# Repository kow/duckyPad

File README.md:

# duckypad: Scriptable Mechanical Keypad with RGB Backlight

duckypad is a mechanical keypad with RGB backlight, OLED screen, and 15 keys. Each key can execute a script when pressed.

The scripts can be as simple as shortcuts like `ctrl+c`, or as complex as [creating root backdoors](https://github.com/hak5darren/USB-Rubber-Ducky/wiki/Payload---OSX-Root-Backdoor) or [grabbing passwords](https://github.com/hak5darren/USB-Rubber-Ducky/wiki/Payload---download-mimikatz%2C-grab-passwords-and-email-them-via-gmail). It's all customizable by you.

Multiple profiles are supported, for different programs/environments.

## Features

* 15 mechanical switches
* Individually addressable RGB backlights with animations
* OLED screen displaying current profile and key functions
* SD card script storage
* Standard duckyscript parsed onboard
* Multiple profiles
* USB-C connector

## Video

Here's a silly video showing duckypad in action, as well as the timelapse of me building it.

https://www.youtube.com/watch?v=EGLLCtRuEuM

## Getting started

Please see [this guide](./getting_started.md) on how to use your duckypad.

## Making one yourself

Please see [this guide](./build_it_yourself.md).

## Questions?

Feel free to ask in the issue section, or email me at `dekunukem__gmail__com`.

## kowmod1 ##

replaced LCD with cheaper 4 pin version, uses any ~$3 128x64 oled LCD with VCC,GND,SCL,SDA pinout order (https://www.ebay.ca/itm/0-96-I2C-IIC-SPI-Serial-128X64-White-OLED-LCD-LED-Display-Module-for-Arduino-LR/392728983410)
replaced sk6812 mini with ws2812b mini, added gerber, bom, and cpl for jlcpcb assembly

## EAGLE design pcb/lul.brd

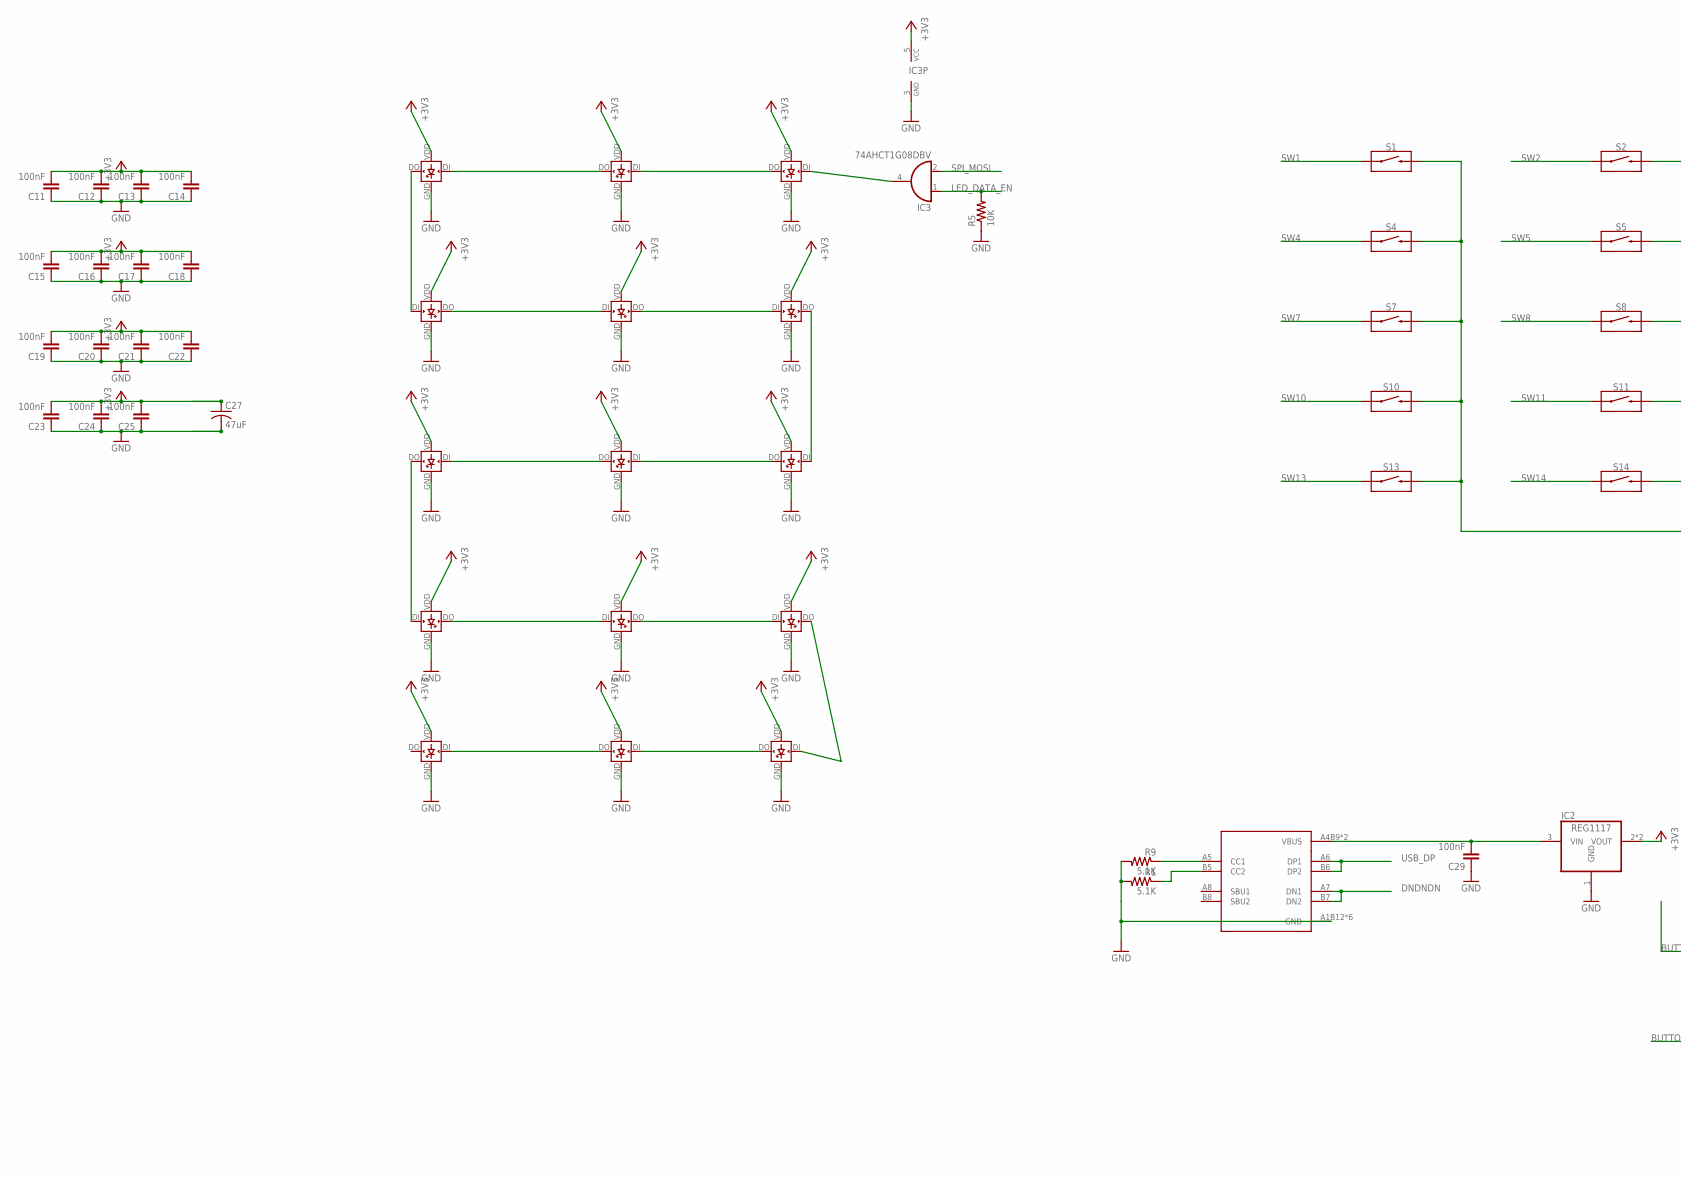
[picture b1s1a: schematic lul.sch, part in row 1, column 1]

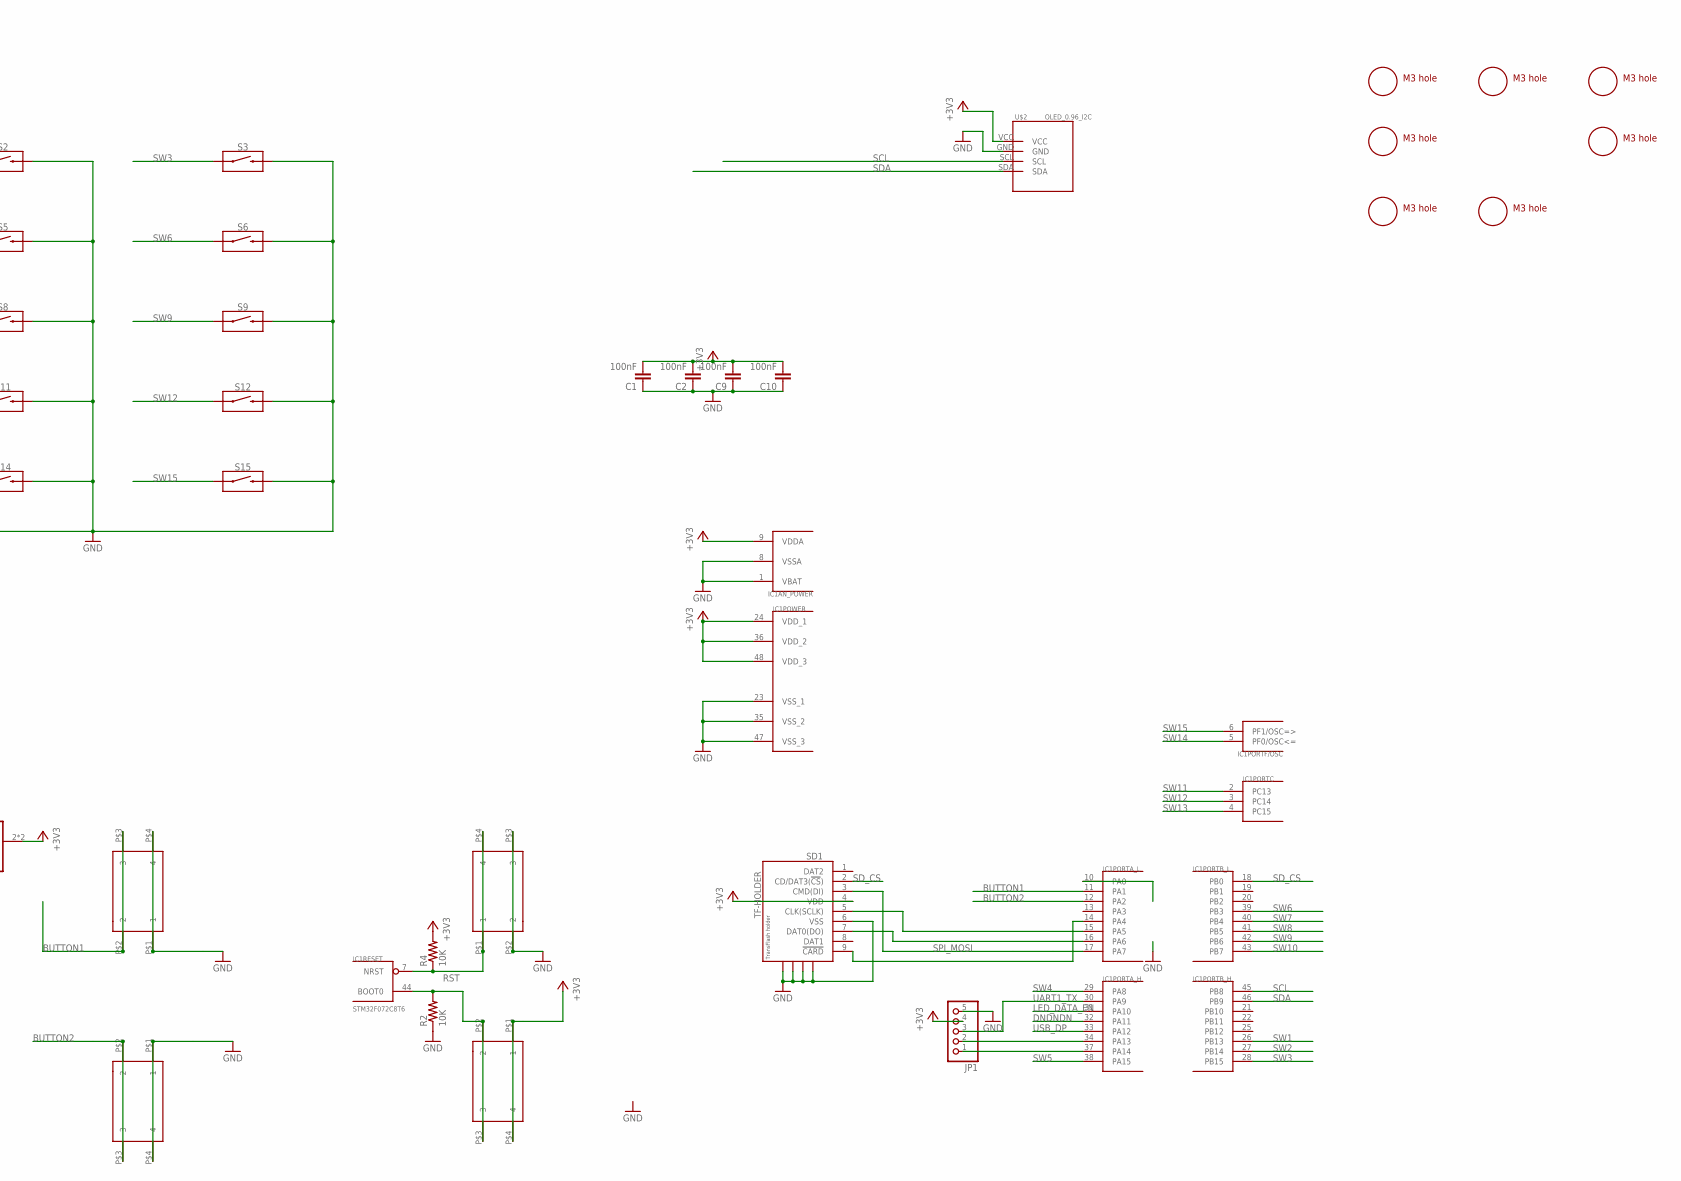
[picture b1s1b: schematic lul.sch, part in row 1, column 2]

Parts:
C1, C2, C9, C10, C11, C12, C13, C14, C15, C16, C17, C18, C19, C20, C21, C22, C23, C24, C25, C29: 100nF; 0805@1
C27: 47uF; C1210
IC1: STM32F072C8T6; TQFP48
IC2: REG1117; SOT223
IC3: 74AHCT1G08DBV; SOT23-5
JP1: PINHD-1X5; 1X05
LED1, LED2, LED3, LED4, LED5, LED6, LED7, LED8, LED9, LED10, LED11, LED12, LED13, LED14, LED15: WS2812B-MINI
R1, R9: 5.1K; 0805
R2, R4, R5: 10K; 0805
S1, S2, S3, S4, S5, S6, S7, S8, S9, S10, S11, S12, S13, S14, S15: CHERRY-MX-LED
SD1: TF-HOLDER; TF-PULL
SW1, SW2, SW3, SW4: 324_SW324_SWITCH_FOOT_HOLE; 342_SWICH_FOOT_HOLE
U2: USBC_16P; USBC_16P_FOOT
U$2: OLED_0.96_I2C
U$7, U$9, U$10, U$11, U$14, U$15, U$16: M3_MOUNTING_HOLE; M3_MOUNTING_HOLE_PACK

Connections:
+3V3: C1.2, C2.2, C9.2, C10.2, C11.2, C12.2, C13.2, C14.2, C15.2, C16.2, C17.2, C18.2, C19.2, C20.2, C21.2, C22.2, C23.2, C24.2, C25.2, C27.1, IC1.9 (VDDA), IC1.24 (VDD_1), IC1.36 (VDD_2), IC1.48 (VDD_3), IC2.2 (VOUT), IC2.4 (VOUT), IC3.5 (VCC), JP1.4, LED1.VDD, LED2.VDD, LED3.VDD, LED4.VDD, LED5.VDD, LED6.VDD, LED7.VDD, LED8.VDD, LED9.VDD, LED10.VDD, LED11.VDD, LED12.VDD, LED13.VDD, LED14.VDD, LED15.VDD, R4.2, SD1.4 (VDD), SW1.P$1 (1), SW1.P$4 (4), U$2.VCC
BUTTON1: IC1.11 (PA1), SW3.P$2 (2), SW3.P$3 (3)
BUTTON2: IC1.12 (PA2), SW4.P$2 (2), SW4.P$3 (3)
DNDNDN: IC1.32 (PA11), U2.A7 (DN1), U2.B7 (DN2)
GND: C1.1, C2.1, C9.1, C10.1, C11.1, C12.1, C13.1, C14.1, C15.1, C16.1, C17.1, C18.1, C19.1, C20.1, C21.1, C22.1, C23.1, C24.1, C25.1, C27.2, C29.1, IC1.1 (VBAT), IC1.8 (VSSA), IC1.23 (VSS_1), IC1.35 (VSS_2), IC1.47 (VSS_3), IC2.1 (GND), IC3.3 (GND), JP1.5, LED1.GND, LED2.GND, LED3.GND, LED4.GND, LED5.GND, LED6.GND, LED7.GND, LED8.GND, LED9.GND, LED10.GND, LED11.GND, LED12.GND, LED13.GND, LED14.GND, LED15.GND, R1.2, R2.1, R5.1, R9.2, S1.S2, S2.S2, S3.S2, S4.S2, S5.S2, S6.S2, S7.S2, S8.S2, S9.S2, S10.S2, S11.S2, S12.S2, S13.S2, S14.S2, S15.S2, SD1.6 (VSS), SD1.S1, SD1.S2, SD1.S3, SD1.S4, SW2.P$2 (2), SW2.P$3 (3), SW3.P$1 (1), SW3.P$4 (4), SW4.P$1 (1), SW4.P$4 (4), U2.A1B12 (GND), U2.B11A12 (GND), U2.P$13 (GND), U2.P$14 (GND), U2.P$15 (GND), U2.P$16 (GND), U$2.GND
LED_DATA_EN: IC1.31 (PA10), IC3.1 (I0), R5.2
unnamed: C29.2, IC2.3 (VIN), U2.A4B9 (VBUS), U2.B4A9 (VBUS)
unnamed: IC1.44 (BOOT0), R2.2, SW1.P$2 (2), SW1.P$3 (3)
unnamed: IC1.15 (PA5), SD1.5 (CLK(SCLK))
unnamed: LED2.DI (DIN), LED3.DO (DOUT)
unnamed: IC1.16 (PA6), SD1.7 (DAT0(DO))
unnamed: IC1.14 (PA4), SD1.9 (!CARD)
unnamed: LED1.DI (DIN), LED2.DO (DOUT)
unnamed: LED1.DO (DOUT), LED4.DI (DIN)
unnamed: LED4.DO (DOUT), LED5.DI (DIN)
unnamed: LED5.DO (DOUT), LED6.DI (DIN)
unnamed: LED6.DO (DOUT), LED9.DI (DIN)
unnamed: LED8.DI (DIN), LED9.DO (DOUT)
unnamed: LED7.DI (DIN), LED8.DO (DOUT)
unnamed: LED7.DO (DOUT), LED10.DI (DIN)
unnamed: LED10.DO (DOUT), LED11.DI (DIN)
unnamed: LED11.DO (DOUT), LED12.DI (DIN)
unnamed: LED12.DO (DOUT), LED15.DI (DIN)
unnamed: LED14.DI (DIN), LED15.DO (DOUT)
unnamed: LED13.DI (DIN), LED14.DO (DOUT)
unnamed: IC3.4 (O), LED3.DI (DIN)
unnamed: R1.1, U2.B5 (CC2)
unnamed: IC1.37 (PA14), JP1.1
unnamed: R9.1, U2.A5 (CC1)
unnamed: IC1.34 (PA13), JP1.2
OLED_RESET: IC1.10 (PA0)
RST: IC1.7 (NRST), R4.1, SW2.P$1 (1), SW2.P$4 (4)
SCL: IC1.45 (PB8), U$2.SCL
SDA: IC1.46 (PB9), U$2.SDA
SD_CS: IC1.18 (PB0), SD1.2 (CD/DAT3(!CS!))
SPI_MOSI: IC1.17 (PA7), IC3.2 (I1), SD1.3 (CMD(DI))
SW1: IC1.26 (PB13), S1.S1
SW2: IC1.27 (PB14), S2.S1
SW3: IC1.28 (PB15), S3.S1
SW4: IC1.29 (PA8), S4.S1
SW5: IC1.38 (PA15), S5.S1
SW6: IC1.39 (PB3), S6.S1
SW7: IC1.40 (PB4), S7.S1
SW8: IC1.41 (PB5), S8.S1
SW9: IC1.42 (PB6), S9.S1
SW10: IC1.43 (PB7), S10.S1
SW11: IC1.2 (PC13), S11.S1
SW12: IC1.3 (PC14), S12.S1
SW13: IC1.4 (PC15), S13.S1
SW14: IC1.5 (PF0/OSC<=), S14.S1
SW15: IC1.6 (PF1/OSC=>), S15.S1
UART1_TX: IC1.30 (PA9), JP1.3
USB_DP: IC1.33 (PA12), U2.A6 (DP1), U2.B6 (DP2)

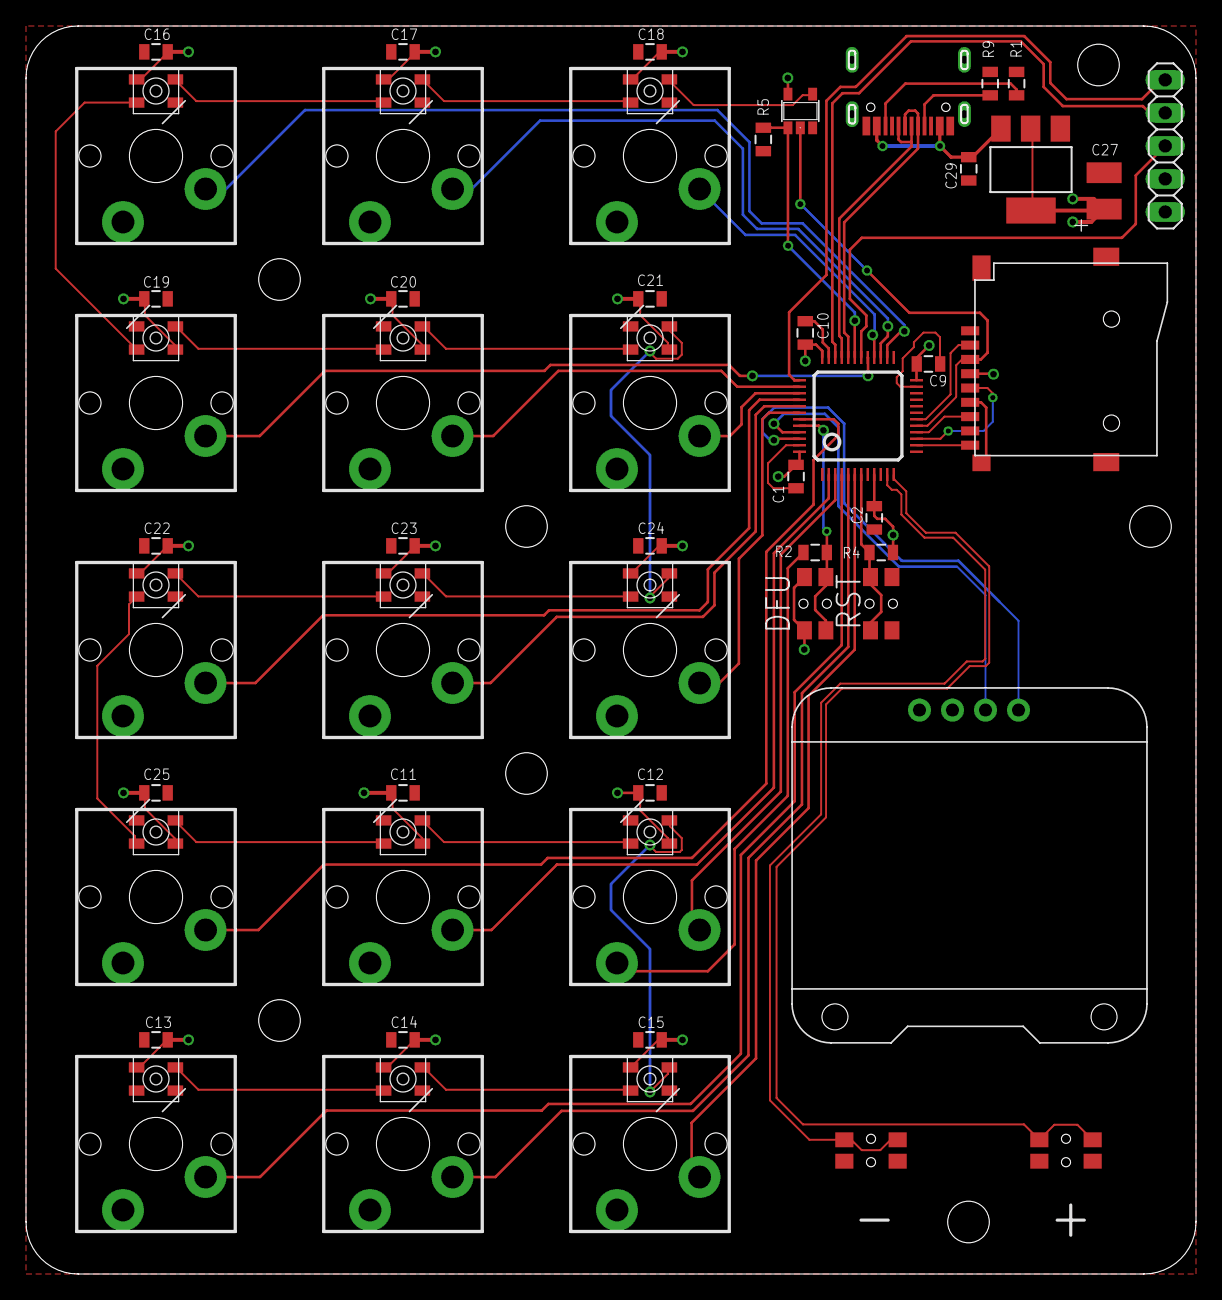
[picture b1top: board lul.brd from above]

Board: 2 copper layers, 90.0 x 96.0 mm, 74 parts (0 on the bottom side), 52 nets.

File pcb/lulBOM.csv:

Comment,Designator,Footprint,LCSC Part #(optional)
100nF,"C1,C2,C9,C10,C11,C12,C13,C14,C15,C16,C17,C18,C19,C20,C21,C22,C23,C24,C25,C29",0805@1,C49678
47uF,"C27",C1210,C77101
STM32F072C8T6,"IC1",TQFP48,C80488
REG1117,"IC2",SOT223,C6186
74AHCT1G08DBV,"IC3",SOT23-5,C113521
WS2812B-MINI,"LED1,LED2,LED3,LED4,LED5,LED6,LED7,LED8,LED9,LED10,LED11,LED12,LED13,LED14,LED15",WS2812B-MINI,C114583
5.1K,"R1,R9",0805,C27834
10K,"R2,R4,R5",0805,C17414
TF-HOLDER,"SD1",TF-PULL,C111196
324_SW324_SWITCH_FOOT_HOLE,"SW1,SW2,SW3,SW4",342_SWICH_FOOT_HOLE,C115360
USBC_16P,"U2",USBC_16P_FOOT,C393939

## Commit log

2020-03-24 simpler version for jlcpcb assembly
